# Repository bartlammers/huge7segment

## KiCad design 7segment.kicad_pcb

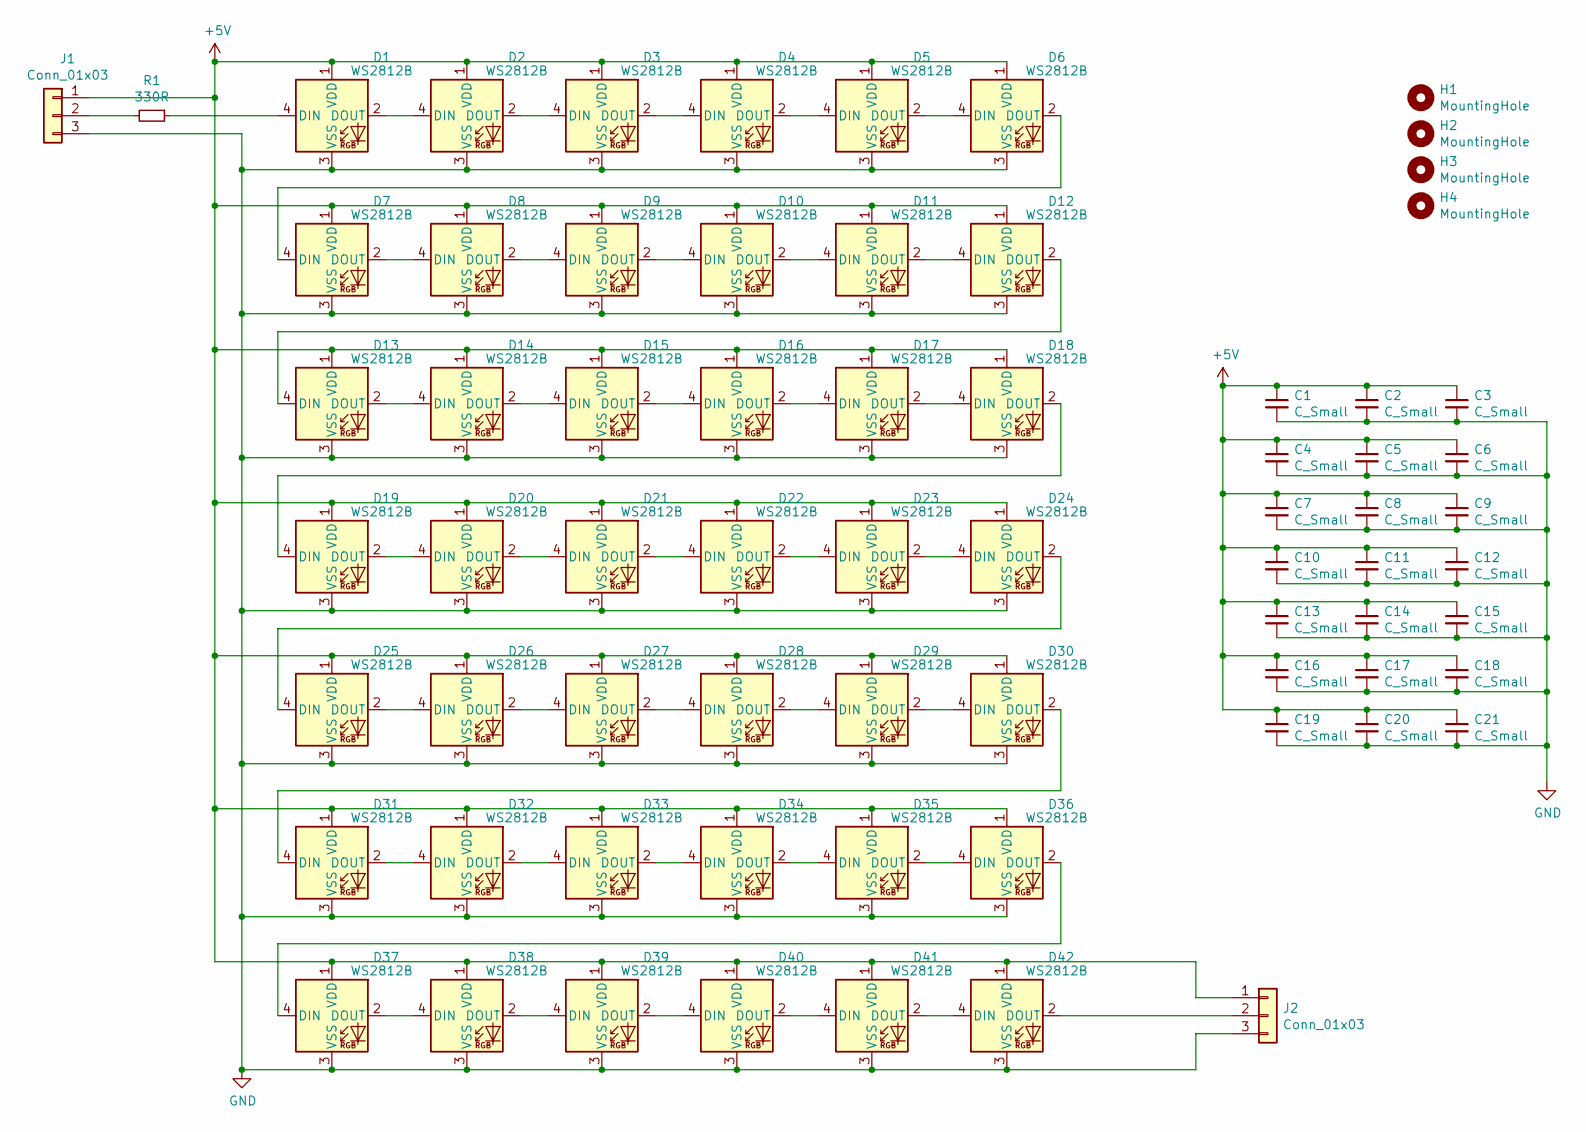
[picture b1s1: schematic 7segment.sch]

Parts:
C1, C2, C3, C4, C5, C6, C7, C8, C9, C10, C11, C12, C13, C14, C15, C16, C17, C18, C19, C20, C21: C_Small; C_0805_2012Metric_Pad1.15x1.40mm_HandSolder
D1, D2, D3, D4, D5, D6, D7, D8, D9, D10, D11, D12, D13, D14, D15, D16, D17, D18, D19, D20, D21, D22, D23, D24, D25, D26, D27, D28, D29, D30, D31, D32, D33, D34, D35, D36, D37, D38, D39, D40, D41, D42: WS2812B; LED_WS2812B_PLCC4_5.0x5.0mm_P3.2mm
H1, H2, H3, H4: MountingHole; MountingHole_3.2mm_M3
J1, J2: Conn_01x03; PinHeader_1x03_P2.54mm_Vertical
R1: 330R; R_0805_2012Metric_Pad1.15x1.40mm_HandSolder

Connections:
+5V: C1.1, C2.1, C3.1, C4.1, C5.1, C6.1, C7.1, C8.1, C9.1, C10.1, C11.1, C12.1, C13.1, C14.1, C15.1, C16.1, C17.1, C18.1, C19.1, C20.1, C21.1, D1.1 (VDD), D2.1 (VDD), D3.1 (VDD), D4.1 (VDD), D5.1 (VDD), D6.1 (VDD), D7.1 (VDD), D8.1 (VDD), D9.1 (VDD), D10.1 (VDD), D11.1 (VDD), D12.1 (VDD), D13.1 (VDD), D14.1 (VDD), D15.1 (VDD), D16.1 (VDD), D17.1 (VDD), D18.1 (VDD), D19.1 (VDD), D20.1 (VDD), D21.1 (VDD), D22.1 (VDD), D23.1 (VDD), D24.1 (VDD), D25.1 (VDD), D26.1 (VDD), D27.1 (VDD), D28.1 (VDD), D29.1 (VDD), D30.1 (VDD), D31.1 (VDD), D32.1 (VDD), D33.1 (VDD), D34.1 (VDD), D35.1 (VDD), D36.1 (VDD), D37.1 (VDD), D38.1 (VDD), D39.1 (VDD), D40.1 (VDD), D41.1 (VDD), D42.1 (VDD), J1.1, J2.1
GND: C1.2, C2.2, C3.2, C4.2, C5.2, C6.2, C7.2, C8.2, C9.2, C10.2, C11.2, C12.2, C13.2, C14.2, C15.2, C16.2, C17.2, C18.2, C19.2, C20.2, C21.2, D1.3 (VSS), D2.3 (VSS), D3.3 (VSS), D4.3 (VSS), D5.3 (VSS), D6.3 (VSS), D7.3 (VSS), D8.3 (VSS), D9.3 (VSS), D10.3 (VSS), D11.3 (VSS), D12.3 (VSS), D13.3 (VSS), D14.3 (VSS), D15.3 (VSS), D16.3 (VSS), D17.3 (VSS), D18.3 (VSS), D19.3 (VSS), D20.3 (VSS), D21.3 (VSS), D22.3 (VSS), D23.3 (VSS), D24.3 (VSS), D25.3 (VSS), D26.3 (VSS), D27.3 (VSS), D28.3 (VSS), D29.3 (VSS), D30.3 (VSS), D31.3 (VSS), D32.3 (VSS), D33.3 (VSS), D34.3 (VSS), D35.3 (VSS), D36.3 (VSS), D37.3 (VSS), D38.3 (VSS), D39.3 (VSS), D40.3 (VSS), D41.3 (VSS), D42.3 (VSS), J1.3, J2.3
unnamed: D1.2 (DOUT), D2.4 (DIN)
unnamed: D1.4 (DIN), R1.1
unnamed: D2.2 (DOUT), D3.4 (DIN)
unnamed: D3.2 (DOUT), D4.4 (DIN)
unnamed: D4.2 (DOUT), D5.4 (DIN)
unnamed: D5.2 (DOUT), D6.4 (DIN)
unnamed: D6.2 (DOUT), D7.4 (DIN)
unnamed: D7.2 (DOUT), D8.4 (DIN)
unnamed: D8.2 (DOUT), D9.4 (DIN)
unnamed: D10.2 (DOUT), D11.4 (DIN)
unnamed: D9.2 (DOUT), D10.4 (DIN)
unnamed: D11.2 (DOUT), D12.4 (DIN)
unnamed: D12.2 (DOUT), D13.4 (DIN)
unnamed: D13.2 (DOUT), D14.4 (DIN)
unnamed: D14.2 (DOUT), D15.4 (DIN)
unnamed: D15.2 (DOUT), D16.4 (DIN)
unnamed: D16.2 (DOUT), D17.4 (DIN)
unnamed: D17.2 (DOUT), D18.4 (DIN)
unnamed: D18.2 (DOUT), D19.4 (DIN)
unnamed: D19.2 (DOUT), D20.4 (DIN)
unnamed: D20.2 (DOUT), D21.4 (DIN)
unnamed: D21.2 (DOUT), D22.4 (DIN)
unnamed: D22.2 (DOUT), D23.4 (DIN)
unnamed: D23.2 (DOUT), D24.4 (DIN)
unnamed: D24.2 (DOUT), D25.4 (DIN)
unnamed: D25.2 (DOUT), D26.4 (DIN)
unnamed: D26.2 (DOUT), D27.4 (DIN)
unnamed: D27.2 (DOUT), D28.4 (DIN)
unnamed: D28.2 (DOUT), D29.4 (DIN)
unnamed: D29.2 (DOUT), D30.4 (DIN)
unnamed: D30.2 (DOUT), D31.4 (DIN)
unnamed: D31.2 (DOUT), D32.4 (DIN)
unnamed: D32.2 (DOUT), D33.4 (DIN)
unnamed: D33.2 (DOUT), D34.4 (DIN)
unnamed: D34.2 (DOUT), D35.4 (DIN)
unnamed: D35.2 (DOUT), D36.4 (DIN)
unnamed: D36.2 (DOUT), D37.4 (DIN)
unnamed: D37.2 (DOUT), D38.4 (DIN)
unnamed: D38.2 (DOUT), D39.4 (DIN)
unnamed: D39.2 (DOUT), D40.4 (DIN)
unnamed: D40.2 (DOUT), D41.4 (DIN)
unnamed: D41.2 (DOUT), D42.4 (DIN)
unnamed: D42.2 (DOUT), J2.2
unnamed: J1.2, R1.2

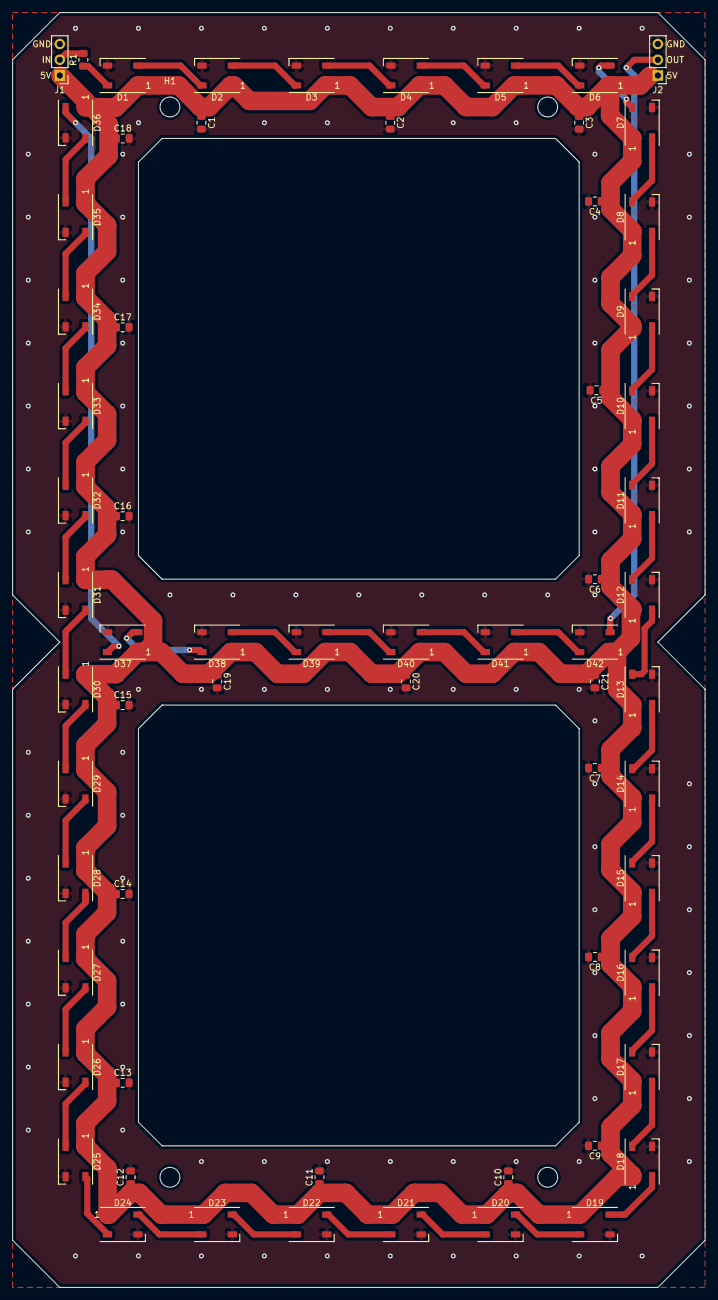
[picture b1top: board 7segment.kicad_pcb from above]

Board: 2 copper layers, 111.8 x 205.7 mm, 70 parts (0 on the bottom side), 46 nets.

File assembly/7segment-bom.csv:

Comment,Designator,Footprint,LCSC
C_Small,"C1,C2,C3,C4,C5,C6,C7,C8,C9,C10,C11,C12,C13,C14,C15,C16,C17,C18,C19,C20,C21",Capacitor_SMD:C_0805_2012Metric_Pad1.15x1.40mm_HandSolder,C49678
WS2812B,"D1,D2,D3,D4,D5,D6,D7,D8,D9,D10,D11,D12,D13,D14,D15,D16,D17,D18,D19,D20,D21,D22,D23,D24,D25,D26,D27,D28,D29,D30,D31,D32,D33,D34,D35,D36,D37,D38,D39,D40,D41,D42",LED_SMD:LED_WS2812B_PLCC4_5.0x5.0mm_P3.2mm,C114586
Conn_01x03,"J1,J2",Connector_PinHeader_2.54mm:PinHeader_1x03_P2.54mm_Vertical,
330R,R1,Resistor_SMD:R_0805_2012Metric_Pad1.15x1.40mm_HandSolder,C17630

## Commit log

2020-10-28 Create LICENSE
2020-10-28 Add labels to connectors
2020-10-28 Add README.md
